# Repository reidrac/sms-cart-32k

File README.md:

SMS Cart project
================

Minimal design limited to 32K (no memory mapper).

**This is a work in progress!**

Licensed under CERN OHL 1.2 terms (see: `cern_ohl_v_1_2.txt` for details).

Juan J. Martinez <jjm@usebox.net>

References:

 - http://www.smspower.org/Development/Documents
 - http://little-scale.blogspot.co.uk/2008/06/how-to-make-32kb-sega-master-system.html
 - Edge connector for KiCad from this thread: http://www.smspower.org/forums/13046-32KSMSCartridgePCBLayoutFeedbackWantedPlease

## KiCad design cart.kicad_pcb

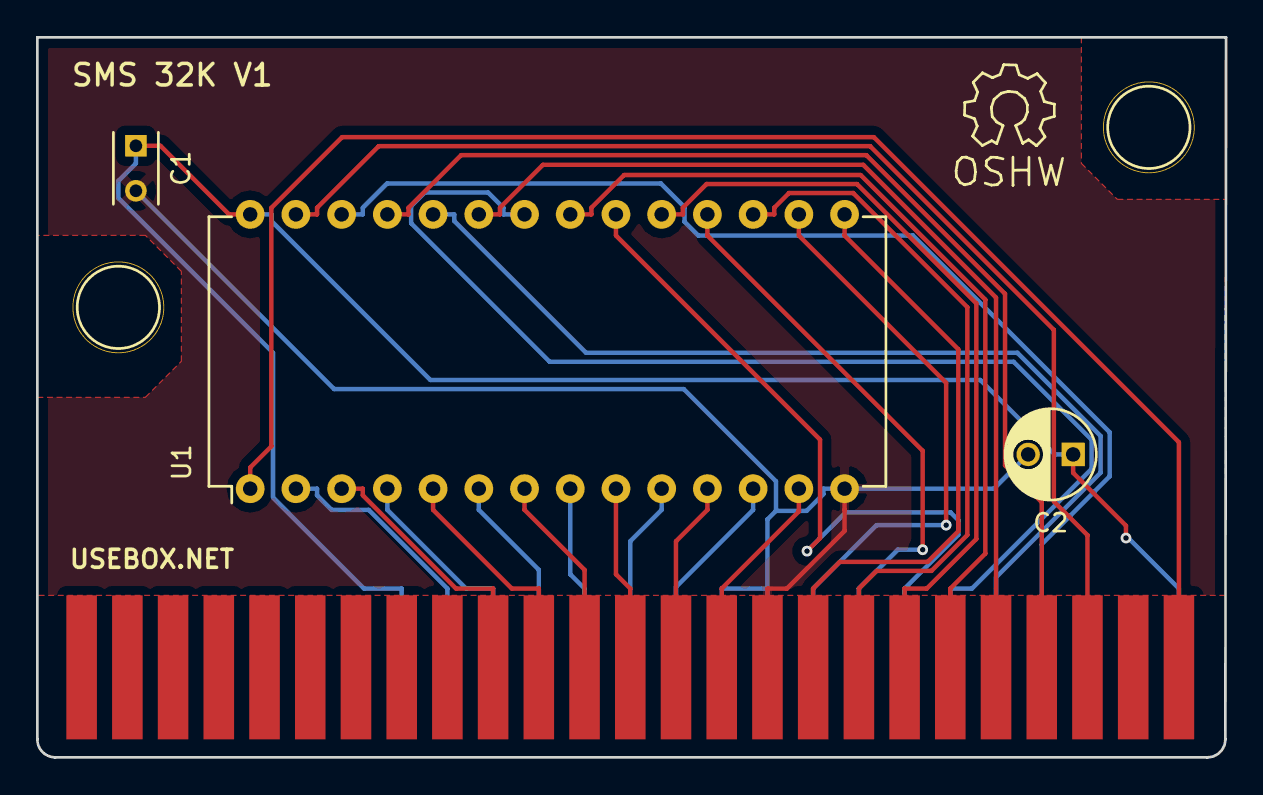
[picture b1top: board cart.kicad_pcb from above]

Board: 2 copper layers, 66.0 x 40.0 mm, 7 parts (0 on the bottom side), 28 nets.

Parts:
C1: 100nF; C_Rect_L4_W2.5_P2.5
C2: 4.7uF; C_Radial_D5_L6_P2.5
OSHW1: Symbol_OSHW-Logo_SilkScreen
P1: CONN_SMS; CONN1
SCREW1, SCREW2: 1pin
U1: 27C256; DIP-28_W15.24mm

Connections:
/a0: P1.25, U1.10
/a1: P1.26, U1.9
/a2: P1.27, U1.8
/a3: P1.28, U1.7
/a4: P1.29, U1.6
/a5: P1.30, U1.5
/a6: P1.31, U1.4
/a7: P1.32, U1.3
/a8: P1.8, U1.25
/a9: P1.9, U1.24
/a10: P1.12, U1.21
/a11: P1.10, U1.23
/a12: P1.33, U1.2
/a13: P1.7, U1.26
/a14: P1.6, U1.27
/a15: P1.2, U1.1
/d0: P1.24, U1.11
/d1: P1.23, U1.12
/d2: P1.22, U1.13
/d3: P1.18, U1.15
/d4: P1.17, U1.16
/d5: P1.16, U1.17
/d6: P1.15, U1.18
/d7: P1.14, U1.19
CE: P1.13, U1.20
GND: C1.2, C2.2, P1.19, P1.20, P1.21, U1.14
OE: P1.11, U1.22
VCC: C1.1, C2.1, P1.1, P1.35, U1.28

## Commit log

2016-07-17 Initial import
2016-07-17 mention the edge connector source
2016-07-17 re-run autorouter
2016-07-17 fixed layer in back pads of the edge connector
2016-07-18 remove solder mask from the connection pins
2016-07-18 make the solder mask free zone bigger
